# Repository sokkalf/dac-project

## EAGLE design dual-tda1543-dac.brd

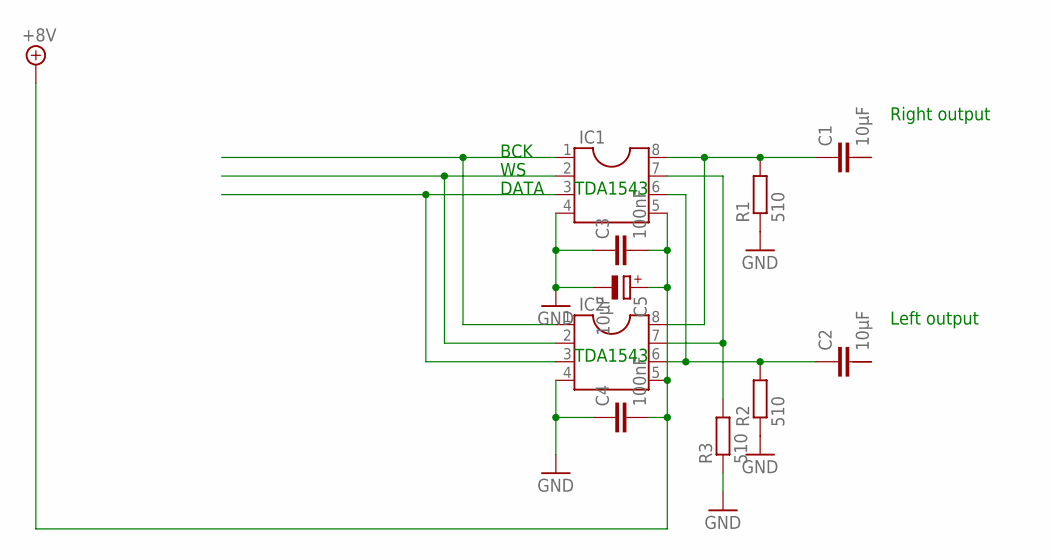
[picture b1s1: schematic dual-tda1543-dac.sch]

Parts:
C1, C2: 10µF; C10-15B6
C3, C4: 100nF; C025-024X044
C5: 10µF; E3,5-8
IC1, IC2: TDA1543S; SOCKED-08
R1, R2, R3: 510; 0207/7

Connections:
+5V: C3.2, C4.2, C5.+, IC1.5 (AOR), IC2.5 (AOR)
GND: C3.1, C4.1, C5.-, IC1.4 (GND), IC2.4 (GND), R1.1, R2.1, R3.1
unnamed: IC1.1 (BCK), IC2.1 (BCK)
unnamed: IC1.2 (WS), IC2.2 (WS)
unnamed: IC1.3 (DATA), IC2.3 (DATA)
unnamed: C2.1, IC1.6 (VREF), IC2.6 (VREF), R2.2
unnamed: C1.1, IC1.8 (VDD), IC2.8 (VDD), R1.2
unnamed: IC1.7 (AOL), IC2.7 (AOL), R3.2

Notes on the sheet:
TDA1543
BCK
DATA
Right output
Left output

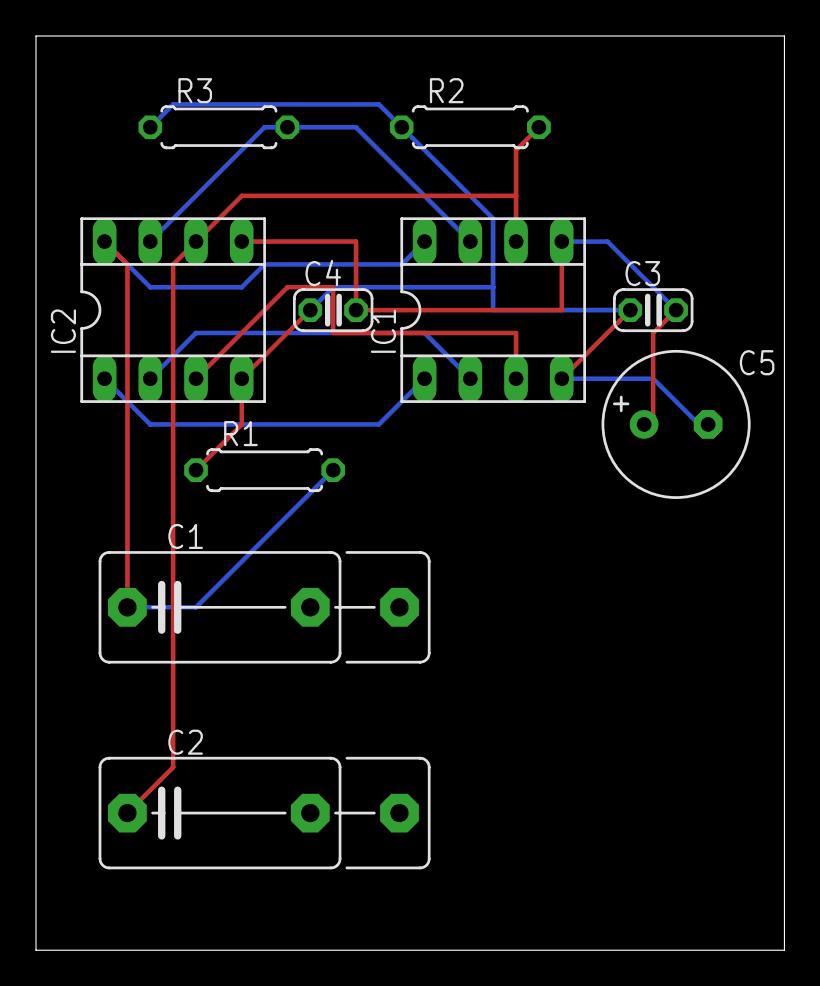
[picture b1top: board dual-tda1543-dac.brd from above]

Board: 2 copper layers, 41.6 x 50.8 mm, 10 parts (0 on the bottom side), 8 nets.

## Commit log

2016-03-14 Unfinished DAC schematic
2016-03-15 Increase delay
